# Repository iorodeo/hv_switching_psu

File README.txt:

hv_switching_psu:  

Design files for IO Rodeo's 25-100V gel electrophoresis power supply. 

contents:

original - contains design files for original version of the  designs (no display).

with_display - contains design files for the latest version with 0-200V digital display.

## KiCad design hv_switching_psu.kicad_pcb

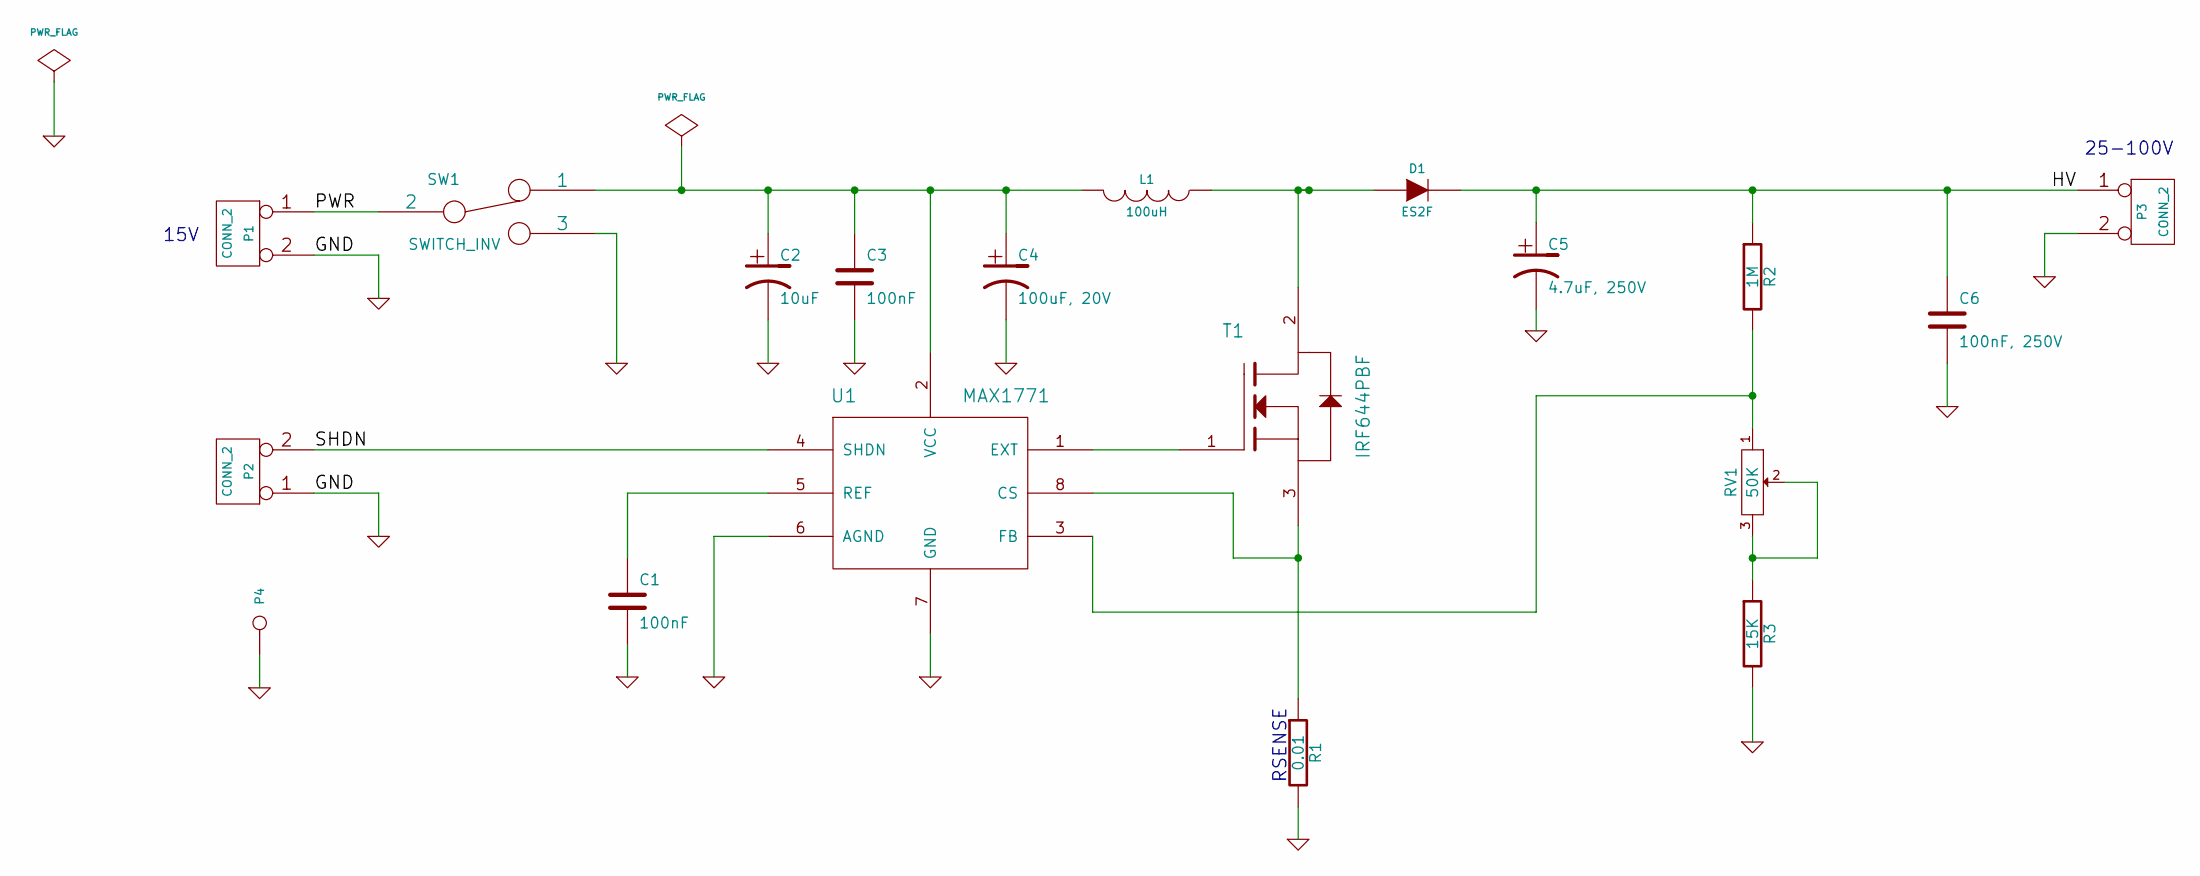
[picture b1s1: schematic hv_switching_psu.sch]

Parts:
C1, C3: 100nF
C2: 10uF
C4: 100uF, 20V
C5: 4.7uF, 250V
C6: 100nF, 250V
D1: ES2F
L1: 100uH
P1, P2, P3: CONN_2
P4: CONN_1
R1: 0.01
R2: 1M
R3: 15K
RV1: 50K
SW1: SWITCH_INV
T1: IRF644PBF
U1: MAX1771

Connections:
/HV: C5.1, C6.1, D1.2 (K), P3.1, R2.1
/PWR: P1.1, SW1.2
/SHDN: P2.2 (PM), U1.4 (SHDN)
GND: C1.2, C2.2, C3.2, C4.2, C5.2, C6.2, P1.2 (PM), P2.1, P3.2 (PM), P4.1, R1.2, R3.2, SW1.3, U1.6 (AGND), U1.7 (GND)
unnamed: T1.1, U1.1 (EXT)
unnamed: R1.1, T1.3, U1.8 (CS)
unnamed: C2.1, C3.1, C4.1, L1.2, SW1.1, U1.2 (VCC)
unnamed: C1.1, U1.5 (REF)
unnamed: D1.1 (A), L1.1, T1.2
unnamed: R3.1, RV1.2, RV1.3
unnamed: R2.2, RV1.1, U1.3 (FB)

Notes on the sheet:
25-100V
RSENSE
15V

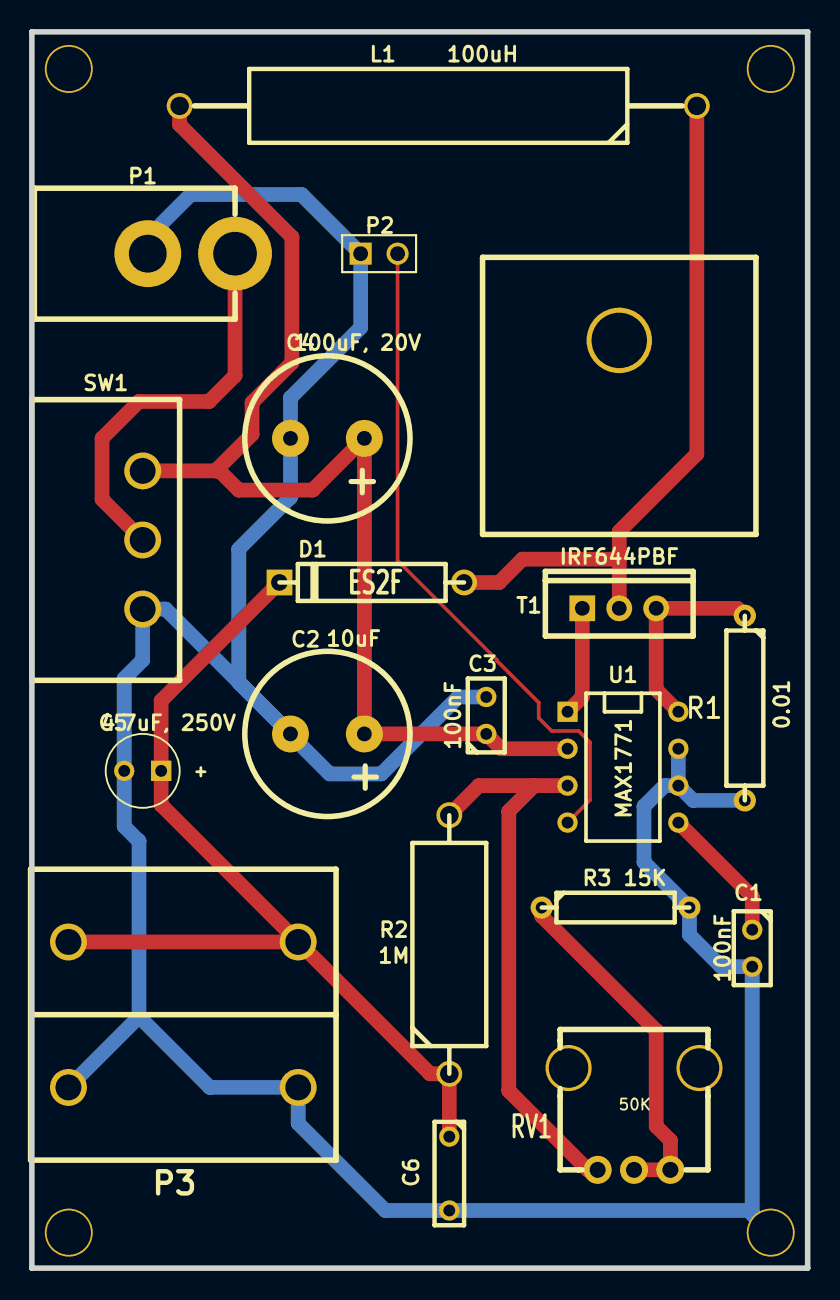
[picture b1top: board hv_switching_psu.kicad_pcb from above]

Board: 2 copper layers, 53.3 x 85.0 mm, 22 parts (0 on the bottom side), 11 nets.

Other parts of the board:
MOUNT_HOLE_1, MOUNT_HOLE_2, MOUNT_HOLE_4: VAL**; MOUNT_HOLE_4_40

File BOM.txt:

PCB components
=========================

Part     Qty   Description                 Vendor    PN                  
------------------------------------------------------------------------

C1, C3   2     100nF, 50V capacitor        Digikey   445-5258-ND	
C2       1     10uF, 250V capacitor        Digikey   P5334-ND	
C4       1     100uF, 50V capacitor        Digikey   P15369CT-ND	
C5       1     4.7uF, 250V capacitor       Digikey   493-1414-ND	
C6       1     100nF, 250V capacitor       Digikey   P10967-ND	
D1       1     ES2F Diode                  Digikey   EGP20G-E3/54GICT-ND	
L1       1     100uH power inductor        Digikey   M8271-ND	
P1       1     DC Jack, 2.1mm              Jameco    137673
P2       1     2x1 pin array               Digikey   SAM1031-50-ND
P3       2     banana jacks                Newark    80P3613 & 80P3616	
R1       1     0.01 ohm resistor           Digikey   LVRA-.01RCT-ND	
R2       1     1 M resistor                Digikey   1MGBCT-ND	
R3       1     10 K resistor               Digikey   A106016CT-ND	
RV1      1     50 K Rotary potentiometer   Digikey   P3C3503-ND	
SW1      1     slide switch                Digikey   CKC5102-ND	
T1       1     IRF644 transistor (FET)     Digikey   IRF644PBF-ND	
U1       1     MAX1771 DC-DC controller    Digikey   MAX1771CPA+-ND	
U1       1     TO220 vertical heat sink    Digikey   A10764-ND


Enclosure hardware
=========================

Qty  Description                                   Vendor      PN                  
--------------------------------------------------------------------------

1    Knob for mounting onto 50K potentiometer      Digikey     226-2092-ND
4    1/4” long, 4-40 round standoff                McMaster    93330A431
4    1” long, 4-40 round standoff                  McMaster    93330A439
12   1/4” long 4-40 machine screws                 McMaster    91249A105
4    3/16” long, 4-40 machine screws               McMaster    91249A102

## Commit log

2012-09-27 Project creation.
2012-09-27 Added banana jacks to BOM.
2013-02-22 Updated design to version 1.1
2013-04-23 Completed new design.
2013-05-13 Updated BOM.
2013-05-13 Added v1.2 gerber files.
2013-05-23 Updated bill of materials.
2013-05-23 Minor editing modification to the BOM.
2013-05-23 Minor editing mod of BOM.
2013-05-23 Minor editing mod.
2013-05-25 Modified resistor settings.
2013-05-25 Save pdf of schematic.
2013-05-25 Added svg of schematic.
2013-05-25 Modified annotations on schematic - changes input and output ranges.
2013-05-25 Added version 1.3 Gerber files.
2013-05-25 Added gerber_v1p3.zip
2013-05-27 Modified silkscreen, remade v1.3 of gerber files.
2013-11-20 Changed R3 in BOM.txt from 15k to 10k.
2013-11-20 Correction changed R3 from 10k to 15k.
2015-01-21 Added version 1.4 of design - fixed issue with switch.
2015-01-21 Added version 1.4 gerver files.
2015-01-21 Added .zipped version of 1.4 gerbers.
2015-01-21 Minor change to kicad_ pcb.
2017-07-12 Grid color modification.
2017-07-12 Updated schematic.
2017-08-05 Added new design with 0-200V display.
2017-08-05 Added 2nd copy of license file.
2017-08-05 Added readme.
2017-08-05 Updated pdfs.
2018-12-20 Re-worked layout for psu with display.
2018-12-24 Added gerber files for new v1.1 version of design with display.
2020-11-05 Add missing part to BOM.
